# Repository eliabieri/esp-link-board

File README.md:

esp-link board
---------------------

### The esp-link firmware
with the esp-link firmware you can remotely programm AVRs,ARMs and even ESP8266s. Additionaly you can use your esp-link board to remotly read the serial port of your projects and thus debug them more easy.
You can get the firmware and more information here: https://github.com/jeelabs/esp-link

### Components

The board is populated with:
- ESP12-e
- AMS1117 regulator (5.5 to 3.3)
- SMD Pushbutton (to toggle GPIO0)
- 2 LEDs (serial and wifi, more information here: https://github.com/jeelabs/esp-link#led-indicators)
- 4 x 10K 0805 Resistor
- 2 x 10uF 0805 Caps

### Pins
I think you understand the marking on your own.
The state pin should be connected to the GPIO0 of the esp8266 you want to program (to toggle GPIO0)

### Picture

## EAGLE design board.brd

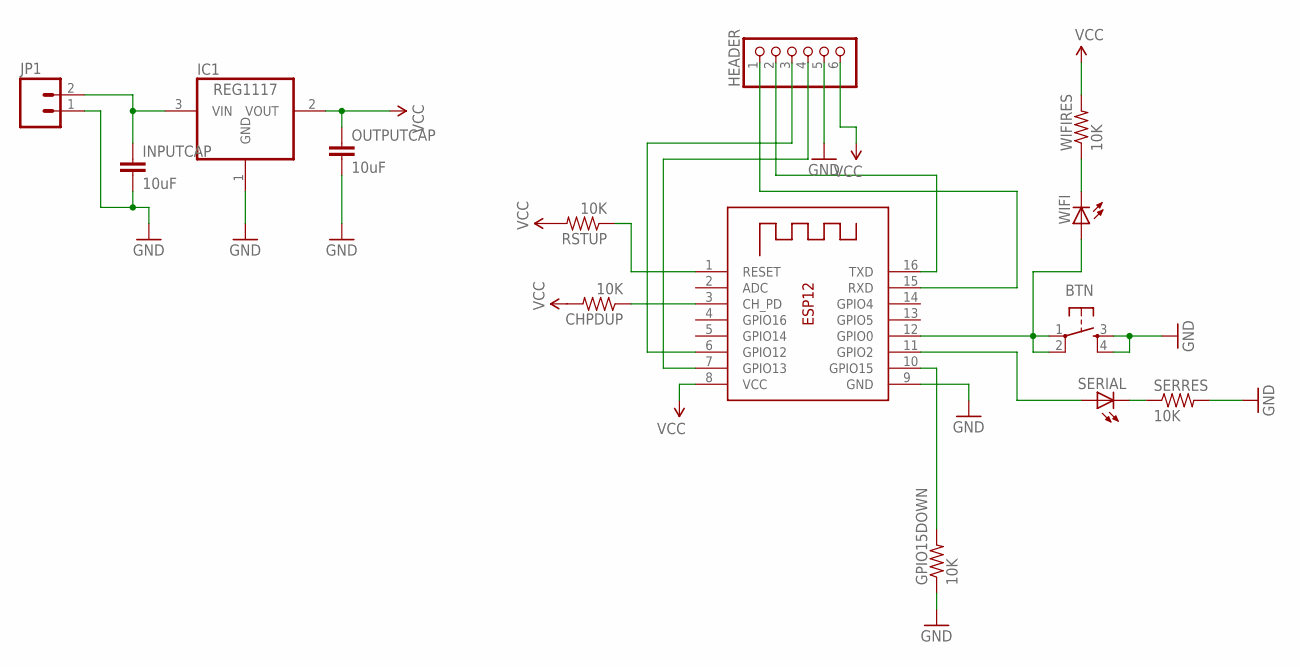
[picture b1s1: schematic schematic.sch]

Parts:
BTN: TAC_SWITCHPTH; TACTILE-PTH
CHPDUP: 10K; 0805
GPIO15DOWN: 10K; 0805
HEADER: PINHD-1X6; 1X06
IC1: REG1117; SOT223
INPUTCAP: 10uF; 0805
JP1: M02LOCK; 1X02_LOCK
OUTPUTCAP: 10uF; 0805
RSTUP: 10K; 0805
SERIAL: LEDCHIPLED_0805; CHIPLED_0805
SERRES: 10K; 0805
WIFI: LEDCHIPLED_0805; CHIPLED_0805
WIFIRES: 10K; 0805
X1: ESP-12

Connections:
GND: BTN.3, BTN.4, GPIO15DOWN.1, HEADER.5, IC1.1 (GND), INPUTCAP.2, JP1.1, OUTPUTCAP.2, SERRES.2, X1.9 (GND)
unnamed: HEADER.1, X1.15 (RXD)
unnamed: HEADER.2, X1.16 (TXD)
unnamed: HEADER.3, X1.6 (GPIO12)
unnamed: HEADER.4, X1.7 (GPIO13)
unnamed: BTN.1, BTN.2, WIFI.A, X1.12 (GPIO0)
unnamed: SERIAL.C, SERRES.1
unnamed: WIFI.C, WIFIRES.1
unnamed: CHPDUP.1, X1.3 (CH_PD)
unnamed: SERIAL.A, X1.11 (GPIO2)
unnamed: GPIO15DOWN.2, X1.10 (GPIO15)
unnamed: RSTUP.1, X1.1 (RESET)
unnamed: IC1.3 (VIN), INPUTCAP.1, JP1.2
VCC: CHPDUP.2, HEADER.6, IC1.2 (VOUT), OUTPUTCAP.1, RSTUP.2, WIFIRES.2, X1.8 (VCC)

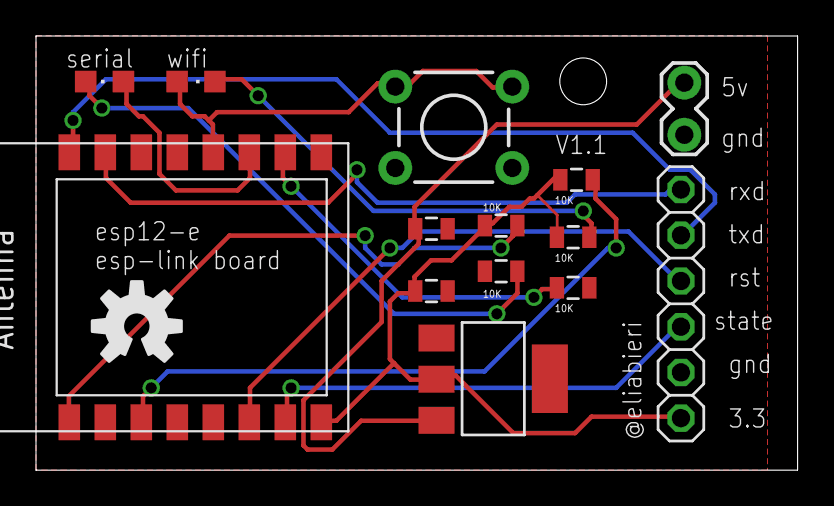
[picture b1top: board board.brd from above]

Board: 2 copper layers, 42.3 x 24.1 mm, 15 parts (0 on the bottom side), 14 nets.

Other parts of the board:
U$1: OSHW-LOGO-M

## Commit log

2016-02-03 added EAGLE files
2016-02-03 added image
2016-02-03 update read
2016-02-03 changed readme
2016-02-03 added pins
2016-02-03 changed led rotation

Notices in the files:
parts and their libraries:
SparkFun-Retired: Licensing:Creative Commons ShareAlike 4.0 International - https://creativecommons.org/licenses/by-sa/4.0
